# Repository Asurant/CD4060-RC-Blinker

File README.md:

# CD4060-RC-Blinker
I made an CD4060 binary blinker that goes through 4 LEDs while using RC timers to slowly turn them on and off. I made it because I wanted to test myself and try to combine the earlier week projects with this current week's project.  

## Hardware

[KiCanvas Link](https://kicanvas.org/?repo=https%3A%2F%2Fgithub.com%2FAsurant%2FCD4060-RC-Blinker%2Ftree%2Fmain%2Fsrc%2Fkicad)
### Schematic

### PCB

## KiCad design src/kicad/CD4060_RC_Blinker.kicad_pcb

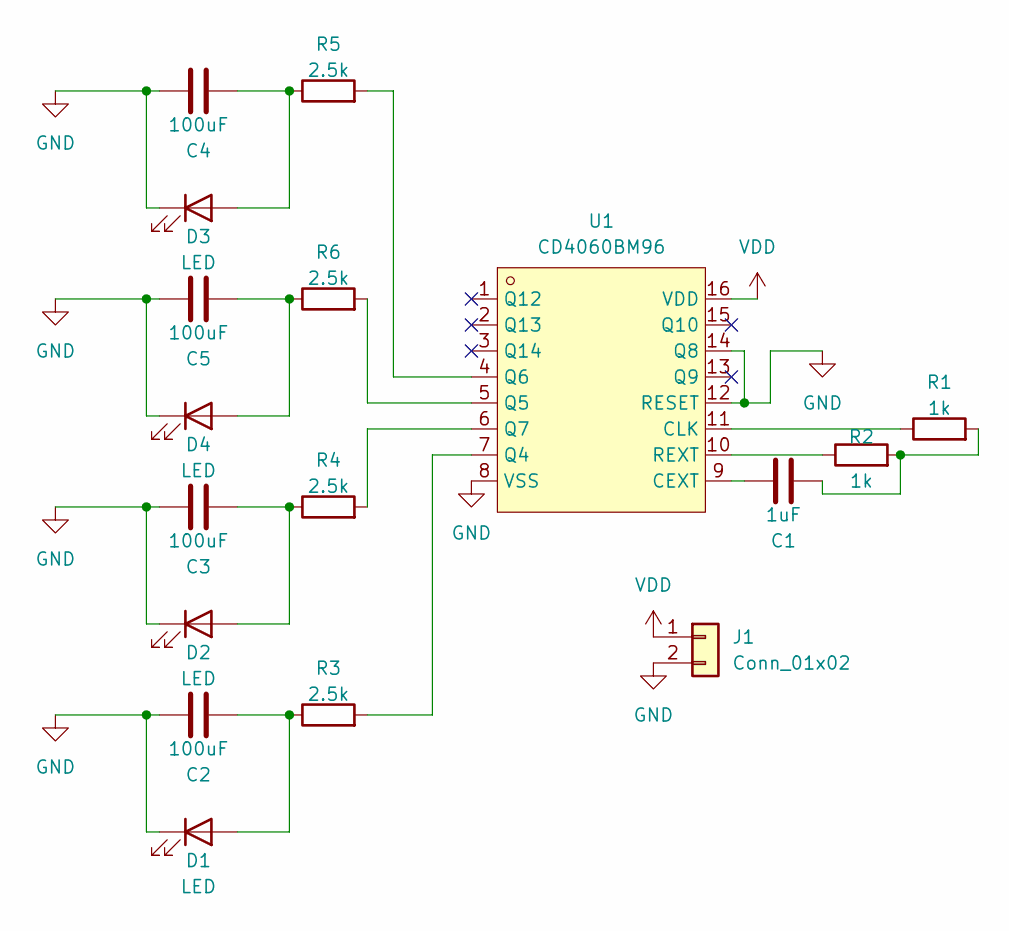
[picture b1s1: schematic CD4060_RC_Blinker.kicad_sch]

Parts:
C1: 1uF; C_Disc_D5.0mm_W2.5mm_P5.00mm
C2, C3, C4, C5: 100uF; C_Disc_D5.0mm_W2.5mm_P5.00mm
D1, D2, D3, D4: LED; LED_D5.0mm
J1: Conn_01x02; PinHeader_1x02_P2.54mm_Vertical
R1, R2: 1k; R_Axial_DIN0204_L3.6mm_D1.6mm_P7.62mm_Horizontal
R3, R4, R5, R6: 2.5k; R_Axial_DIN0204_L3.6mm_D1.6mm_P7.62mm_Horizontal
U1: CD4060BM96; SOIC-16_L9.9-W3.9-P1.27-LS6.0-BL; MPN CD4060BM96; LCSC Part C32699

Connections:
GND: C2.2, C3.2, C4.2, C5.2, D1.1 (K), D2.1 (K), D3.1 (K), D4.1 (K), J1.2, U1.8 (VSS), U1.12 (RESET), U1.14 (Q8)
unnamed: C1.1, R1.2, R2.2
unnamed: C2.1, D1.2 (A), R3.1
unnamed: C3.1, D2.2 (A), R4.1
unnamed: C4.1, D3.2 (A), R5.1
unnamed: C5.1, D4.2 (A), R6.1
unnamed: C1.2, U1.9 (CEXT)
unnamed: R1.1, U1.11 (CLK)
unnamed: R3.2, U1.7 (Q4)
unnamed: R6.2, U1.5 (Q5)
unnamed: R5.2, U1.4 (Q6)
unnamed: R4.2, U1.6 (Q7)
unnamed: R2.1, U1.10 (REXT)
VDD: J1.1, U1.16 (VDD)

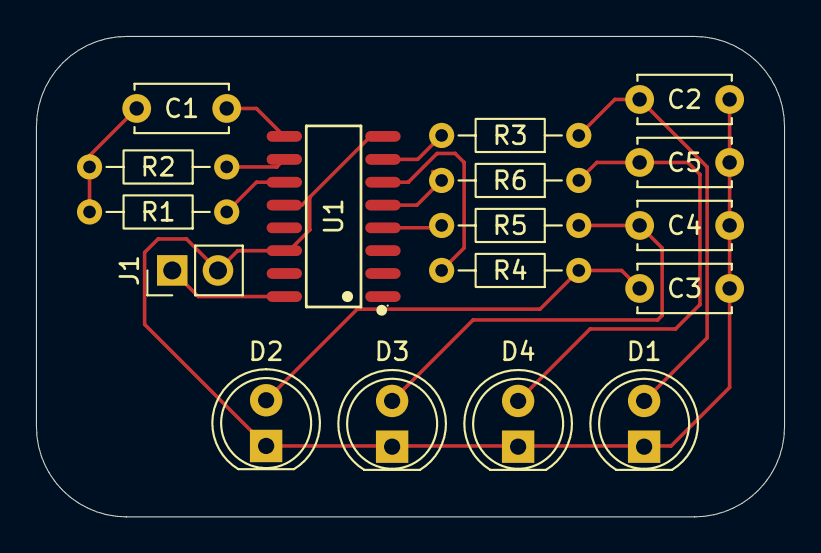
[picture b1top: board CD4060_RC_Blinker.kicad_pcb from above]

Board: 2 copper layers, 41.6 x 26.7 mm, 17 parts (0 on the bottom side), 14 nets.

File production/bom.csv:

Designator,Footprint,Quantity,Value,LCSC Part #
C1,C_Disc_D5.0mm_W2.5mm_P5.00mm,1,1uF,
"C2, C3, C4, C5",C_Disc_D5.0mm_W2.5mm_P5.00mm,4,100uF,
"D1, D2, D3, D4",LED_D5.0mm,4,LED,
J1,PinHeader_1x02_P2.54mm_Vertical,1,Conn_01x02,
"R1, R2",R_Axial_DIN0204_L3.6mm_D1.6mm_P7.62mm_Horizontal,2,1k,
"R3, R4, R5, R6",R_Axial_DIN0204_L3.6mm_D1.6mm_P7.62mm_Horizontal,4,2.5k,
U1,SOIC-16_L9.9-W3.9-P1.27-LS6.0-BL,1,CD4060BM96,C32699

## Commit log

2026-05-19 Update journal.md
    When copy and pasting previous journal entries to make new ones I forgot to update the date
